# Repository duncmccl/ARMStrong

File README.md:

# ARMStrong
Microcontroller Learner board replacement for the BASYS MX3

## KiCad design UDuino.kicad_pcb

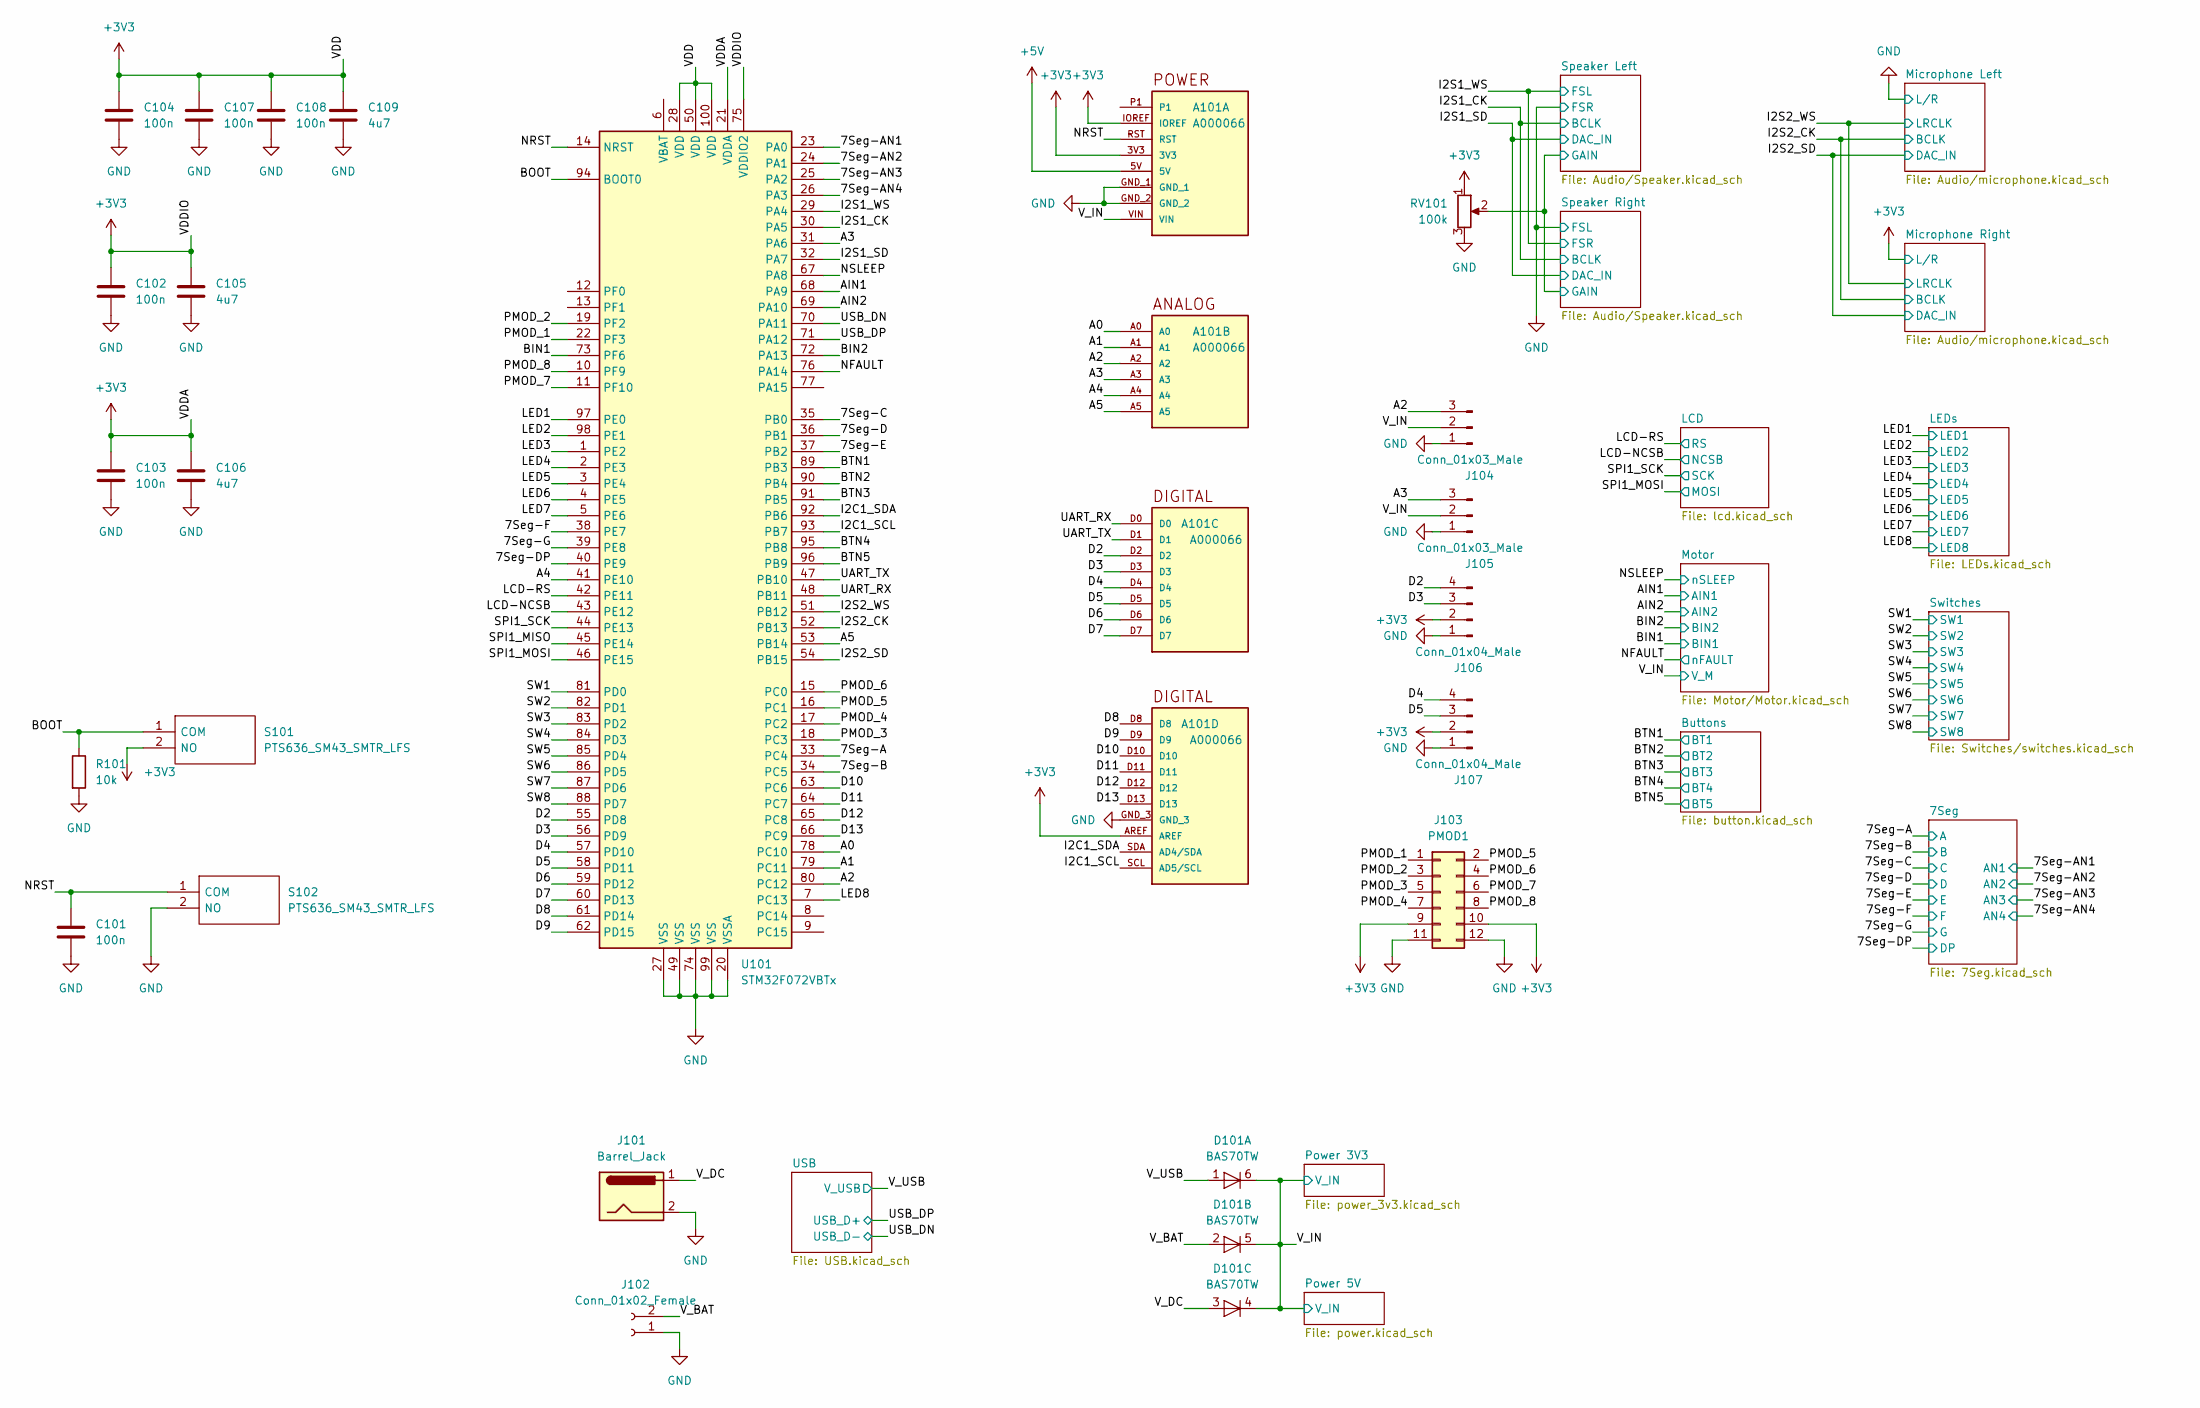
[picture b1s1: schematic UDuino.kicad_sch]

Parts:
A101: A000066; ARDUINO_A000066; Manufacturer_Part_Number A000066
C101, C102, C103, C104, C107, C108: 100n; C_0805_2012Metric; Manufacturer_Part_Number CL21B104KCFNNNE
C105, C106, C109: 4u7; C_0603_1608Metric; Manufacturer_Part_Number CL10A475KO8NNNC
D101: BAS70TW; SOT-363_SC-70-6; Manufacturer_Part_Number BAS70TW
J101: Barrel_Jack; BarrelJack_Horizontal; Manufacturer_Part_Number G-1005B
J102: Conn_01x02_Female; JST_XH_B2B-XH-AM_1x02_P2.50mm_Vertical
J103: PMOD1; PinSocket_2x06_P2.54mm_Horizontal
J104, J105: Conn_01x03_Male; PinHeader_1x03_P2.54mm_Vertical
J106, J107: Conn_01x04_Male; PinHeader_1x04_P2.54mm_Vertical
R101: 10k; R_0603_1608Metric; Manufacturer_Part_Number 0603WAF1002T5E
RV101: 100k; TRIM_3352T-1-104LF
S101, S102: PTS636_SM43_SMTR_LFS; PTS636SM43SMTRLFS; Mouser Part Number 611-PTS636SM43SMTRLF
U101: STM32F072VBTx; LQFP-100_14x14mm_P0.5mm

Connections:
+3V3: A101.3V3, A101.AREF, A101.IOREF, C102.2, C103.2, C104.2, C105.2, C106.2, C107.2, C108.2, C109.2, J103.9, J103.10, J106.2, J107.2, RV101.1, S101.2 (NO), U101.21 (VDDA), U101.28 (VDD), U101.50 (VDD), U101.75 (VDDIO2), U101.100 (VDD); also elsewhere on the board
+5V: A101.5V; also elsewhere on the board
/7Seg-A: U101.33 (PC4); also elsewhere on the board
/7Seg-AN1: U101.23 (PA0); also elsewhere on the board
/7Seg-AN2: U101.24 (PA1); also elsewhere on the board
/7Seg-AN3: U101.25 (PA2); also elsewhere on the board
/7Seg-AN4: U101.26 (PA3); also elsewhere on the board
/7Seg-B: U101.34 (PC5); also elsewhere on the board
/7Seg-C: U101.35 (PB0); also elsewhere on the board
/7Seg-D: U101.36 (PB1); also elsewhere on the board
/7Seg-DP: U101.40 (PE9); also elsewhere on the board
/7Seg-E: U101.37 (PB2); also elsewhere on the board
/7Seg-F: U101.38 (PE7); also elsewhere on the board
/7Seg-G: U101.39 (PE8); also elsewhere on the board
/A0: A101.A0, U101.78 (PC10)
/A1: A101.A1, U101.79 (PC11)
/A2: A101.A2, J104.3, U101.80 (PC12)
/A3: A101.A3, J105.3, U101.31 (PA6)
/A4: A101.A4, U101.41 (PE10)
/A5: A101.A5, U101.53 (PB14)
/AIN1: U101.68 (PA9); also elsewhere on the board
/AIN2: U101.69 (PA10); also elsewhere on the board
/BIN1: U101.73 (PF6); also elsewhere on the board
/BIN2: U101.72 (PA13); also elsewhere on the board
/BOOT: R101.1, S101.1 (COM), U101.94 (BOOT0)
/BTN1: U101.89 (PB3); also elsewhere on the board
/BTN2: U101.90 (PB4); also elsewhere on the board
/BTN3: U101.91 (PB5); also elsewhere on the board
/BTN4: U101.95 (PB8); also elsewhere on the board
/BTN5: U101.96 (PB9); also elsewhere on the board
/D2: A101.D2, J106.4, U101.55 (PD8)
/D3: A101.D3, J106.3, U101.56 (PD9)
/D4: A101.D4, J107.4, U101.57 (PD10)
/D5: A101.D5, J107.3, U101.58 (PD11)
/D6: A101.D6, U101.59 (PD12)
/D7: A101.D7, U101.60 (PD13)
/D8: A101.D8, U101.61 (PD14)
/D9: A101.D9, U101.62 (PD15)
/D10: A101.D10, U101.63 (PC6)
/D11: A101.D11, U101.64 (PC7)
/D12: A101.D12, U101.65 (PC8)
/D13: A101.D13, U101.66 (PC9)
/I2C1_SCL: A101.SCL (AD5/SCL), U101.93 (PB7)
/I2C1_SDA: A101.SDA (AD4/SDA), U101.92 (PB6)
/I2S1_CK: U101.30 (PA5); also elsewhere on the board
/I2S1_SD: U101.32 (PA7); also elsewhere on the board
/I2S1_WS: U101.29 (PA4); also elsewhere on the board
/I2S2_CK: U101.52 (PB13); also elsewhere on the board
/I2S2_SD: U101.54 (PB15); also elsewhere on the board
/I2S2_WS: U101.51 (PB12); also elsewhere on the board
/LCD-NCSB: U101.43 (PE12); also elsewhere on the board
/LCD-RS: U101.42 (PE11); also elsewhere on the board
/LED1: U101.97 (PE0); also elsewhere on the board
/LED2: U101.98 (PE1); also elsewhere on the board
/LED3: U101.1 (PE2); also elsewhere on the board
/LED4: U101.2 (PE3); also elsewhere on the board
/LED5: U101.3 (PE4); also elsewhere on the board
/LED6: U101.4 (PE5); also elsewhere on the board
/LED7: U101.5 (PE6); also elsewhere on the board
/LED8: U101.7 (PC13); also elsewhere on the board
/NFAULT: U101.76 (PA14); also elsewhere on the board
/NRST: A101.RST, C101.2, S102.1 (COM), U101.14 (NRST)
/NSLEEP: U101.67 (PA8); also elsewhere on the board
/PMOD_1: J103.1, U101.22 (PF3)
/PMOD_2: J103.3, U101.19 (PF2)
/PMOD_3: J103.5, U101.18 (PC3)
/PMOD_4: J103.7, U101.17 (PC2)
/PMOD_5: J103.2, U101.16 (PC1)
/PMOD_6: J103.4, U101.15 (PC0)
/PMOD_7: J103.6, U101.11 (PF10)
/PMOD_8: J103.8, U101.10 (PF9)
/SPI1_MISO: U101.45 (PE14)
/SPI1_MOSI: U101.46 (PE15); also elsewhere on the board
/SPI1_SCK: U101.44 (PE13); also elsewhere on the board
/SW1: U101.81 (PD0); also elsewhere on the board
/SW2: U101.82 (PD1); also elsewhere on the board
/SW3: U101.83 (PD2); also elsewhere on the board
/SW4: U101.84 (PD3); also elsewhere on the board
/SW5: U101.85 (PD4); also elsewhere on the board
/SW6: U101.86 (PD5); also elsewhere on the board
/SW7: U101.87 (PD6); also elsewhere on the board
/SW8: U101.88 (PD7); also elsewhere on the board
/Speaker Left/GAIN: RV101.2; also elsewhere on the board
/UART_RX: A101.D0, U101.48 (PB11)
/UART_TX: A101.D1, U101.47 (PB10)
/USB_DN: U101.70 (PA11); also elsewhere on the board
/USB_DP: U101.71 (PA12); also elsewhere on the board
/V_BAT: D101.2 (A), J102.2
/V_DC: D101.3 (A), J101.1
/V_IN: A101.VIN, D101.4 (K), D101.5 (K), D101.6 (K), J104.2, J105.2; also elsewhere on the board
/V_USB: D101.1 (A); also elsewhere on the board
GND: A101.GND_1, A101.GND_2, A101.GND_3, C101.1, C102.1, C103.1, C104.1, C105.1, C106.1, C107.1, C108.1, C109.1, J101.2, J102.1, J103.11, J103.12, J104.1, J105.1, J106.1, J107.1, R101.2, RV101.3, S102.2 (NO), U101.20 (VSSA), U101.27 (VSS), U101.49 (VSS), U101.74 (VSS), U101.99 (VSS); also elsewhere on the board

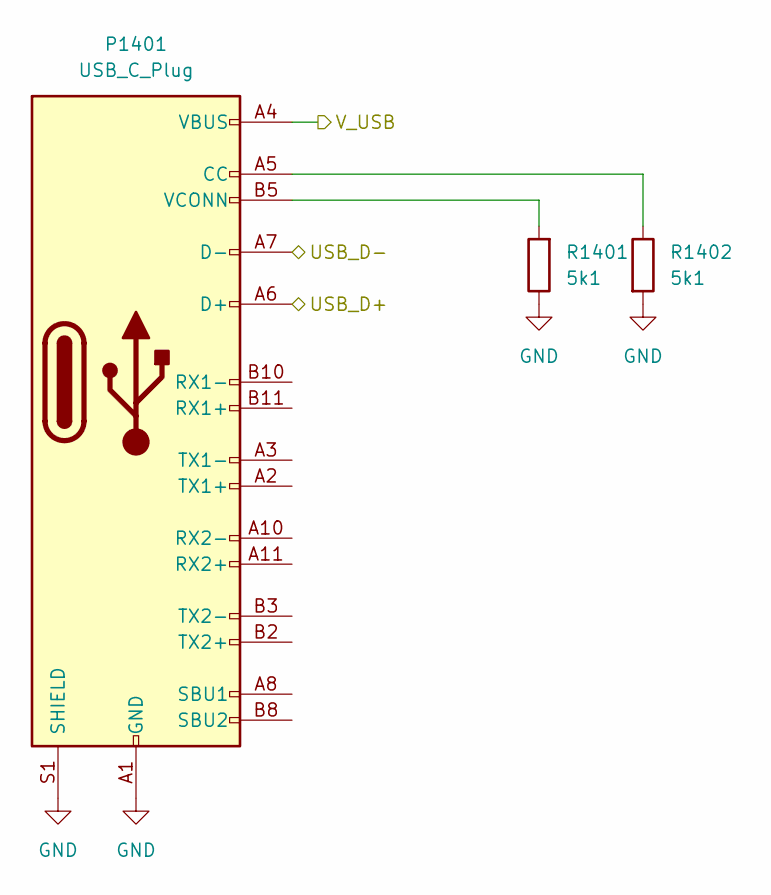
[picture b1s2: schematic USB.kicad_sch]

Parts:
P1401: USB_C_Plug; USB_C_Receptacle_Palconn_UTC16-G
R1401, R1402: 5k1; R_0603_1608Metric; Manufacturer_Part_Number 0603WAF5101T5E

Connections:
/USB_DN: P1401.A7 (D-); also elsewhere on the board
/USB_DP: P1401.A6 (D+); also elsewhere on the board
/V_USB: P1401.A4 (VBUS), P1401.A9 (VBUS), P1401.B4 (VBUS), P1401.B9 (VBUS); also elsewhere on the board
GND: P1401.A1 (GND), P1401.A12 (GND), P1401.B1 (GND), P1401.B12 (GND), P1401.S1 (SHIELD), R1401.1, R1402.2; also elsewhere on the board
unnamed: P1401.A5 (CC), R1402.1
unnamed: P1401.B5 (VCONN), R1401.2

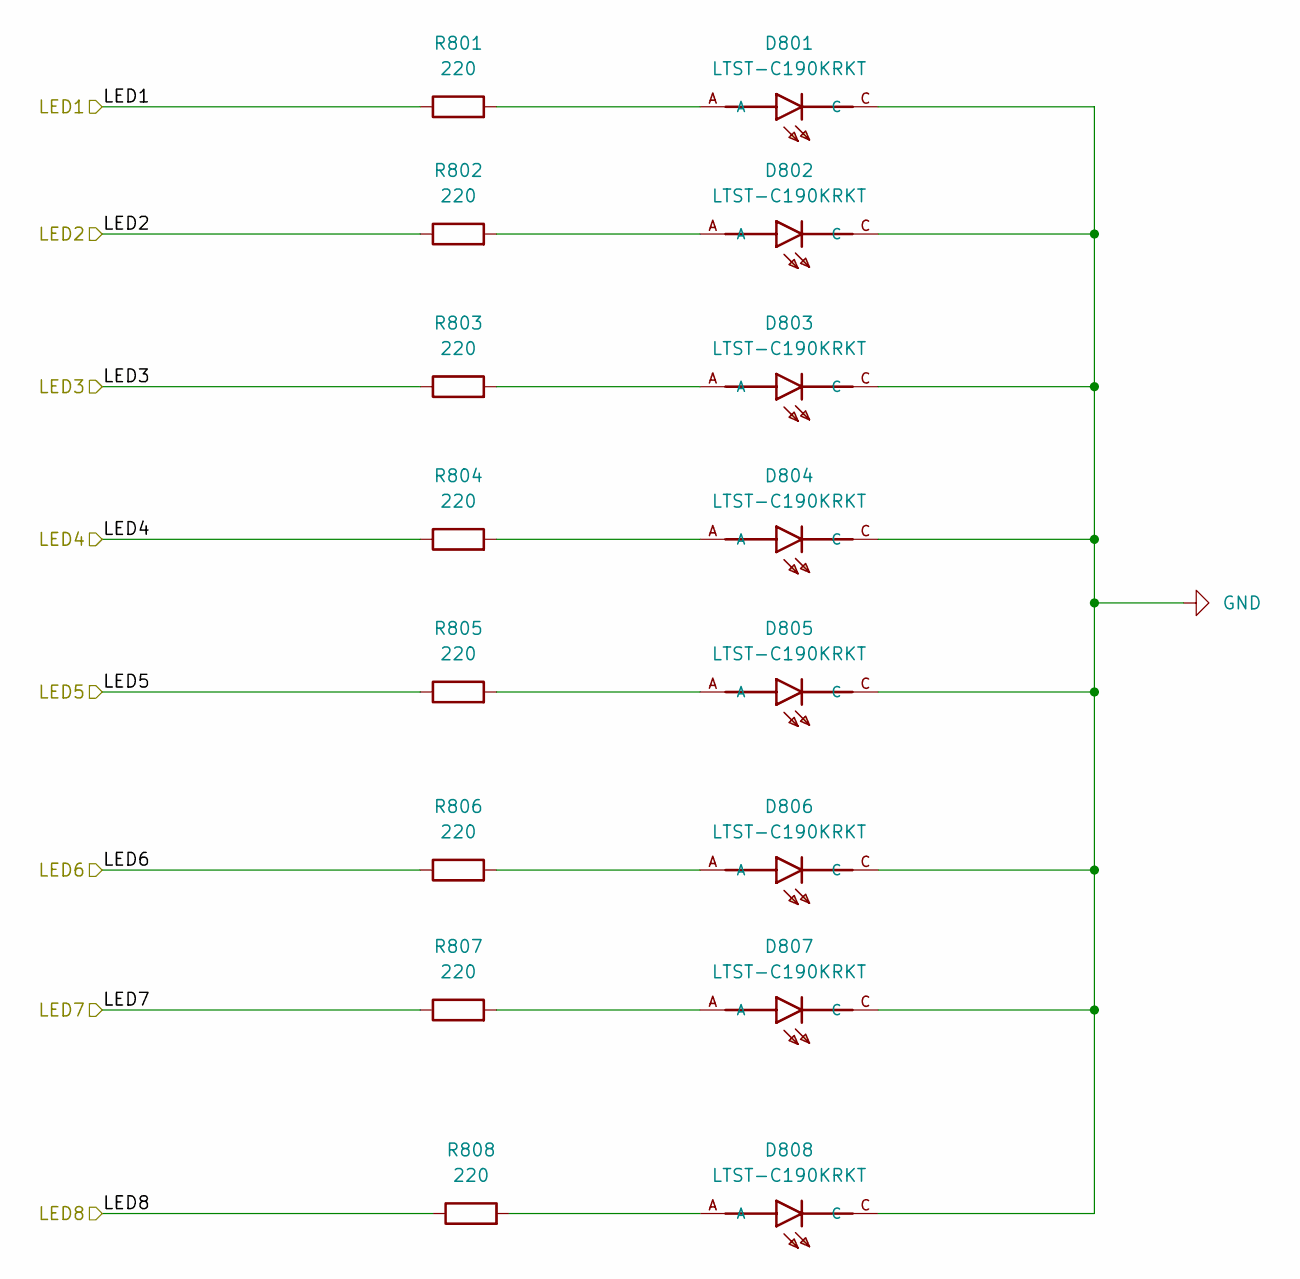
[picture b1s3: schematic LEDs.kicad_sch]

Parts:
D801, D802, D803, D804, D805, D806, D807, D808: LTST-C190KRKT; LEDC1608X35N; Manufacturer_Part_Number LTST-C190KRKT
R801, R802, R803, R804, R805, R806, R807, R808: 220; R_0603_1608Metric; Manufacturer_Part_Number 0603WAF2200T5E

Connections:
/LED1: R801.1; also elsewhere on the board
/LED2: R802.1; also elsewhere on the board
/LED3: R803.1; also elsewhere on the board
/LED4: R804.1; also elsewhere on the board
/LED5: R805.1; also elsewhere on the board
/LED6: R806.1; also elsewhere on the board
/LED7: R807.1; also elsewhere on the board
/LED8: R808.1; also elsewhere on the board
GND: D801.C, D802.C, D803.C, D804.C, D805.C, D806.C, D807.C, D808.C; also elsewhere on the board
unnamed: D801.A, R801.2
unnamed: D802.A, R802.2
unnamed: D803.A, R803.2
unnamed: D804.A, R804.2
unnamed: D805.A, R805.2
unnamed: D806.A, R806.2
unnamed: D807.A, R807.2
unnamed: D808.A, R808.2

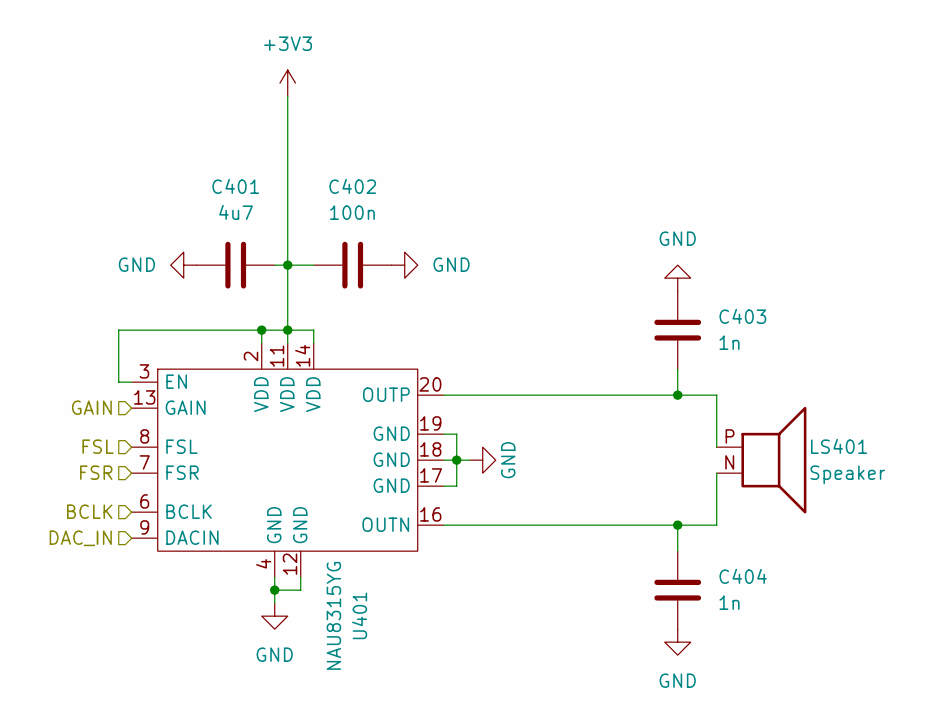
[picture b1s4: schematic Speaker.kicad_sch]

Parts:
C401: 4u7; C_0603_1608Metric; Manufacturer_Part_Number CL10A475KO8NNNC
C402: 100n; C_0805_2012Metric; Manufacturer_Part_Number CL21B104KCFNNNE
C403, C404: 1n; C_0603_1608Metric; Manufacturer_Part_Number CL10B102KB8NNNC
LS401: Speaker; SPKR_AS01508MS-SC11-WP-R
U401: NAU8315YG; QFN50P400X400X80-21N

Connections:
+3V3: C401.2, C402.1, U401.2 (VDD), U401.3 (EN), U401.11 (VDD), U401.14 (VDD); also elsewhere on the board
/I2S1_CK: U401.6 (BCLK); also elsewhere on the board
/I2S1_SD: U401.9 (DACIN); also elsewhere on the board
/I2S1_WS: U401.8 (FSL); also elsewhere on the board
/Speaker Left/GAIN: U401.13 (GAIN); also elsewhere on the board
GND: C401.1, C402.2, C403.1, C404.2, U401.4 (GND), U401.7 (FSR), U401.12 (GND), U401.17 (GND), U401.18 (GND), U401.19 (GND); also elsewhere on the board
unnamed: C403.2, LS401.P (1), U401.20 (OUTP)
unnamed: C404.1, LS401.N (2), U401.16 (OUTN)

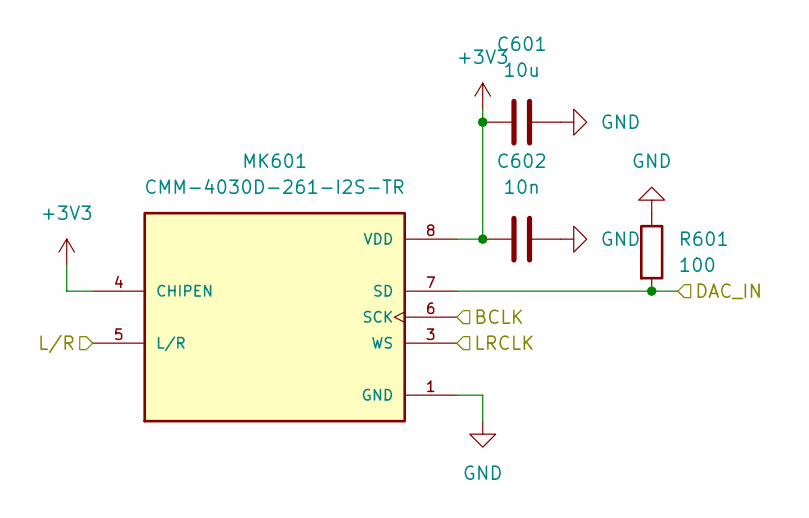
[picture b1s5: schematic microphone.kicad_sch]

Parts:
C601: 10u; C_0603_1608Metric; Manufacturer_Part_Number CL10A106KP8NNNC
C602: 10n; C_0603_1608Metric; Manufacturer_Part_Number 0603B103K500NT
MK601: CMM-4030D-261-I2S-TR; MIC_CMM-4030D-261-I2S-TR; PARTREV 1.0
R601: 100; R_0603_1608Metric; Manufacturer_Part_Number 0603WAF1000T5E

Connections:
+3V3: C601.1, C602.2, MK601.4 (CHIPEN), MK601.8 (VDD); also elsewhere on the board
/I2S2_CK: MK601.6 (SCK); also elsewhere on the board
/I2S2_SD: MK601.7 (SD), R601.2; also elsewhere on the board
/I2S2_WS: MK601.3 (WS); also elsewhere on the board
GND: C601.2, C602.1, MK601.1 (GND), MK601.5 (L/R), R601.1; also elsewhere on the board

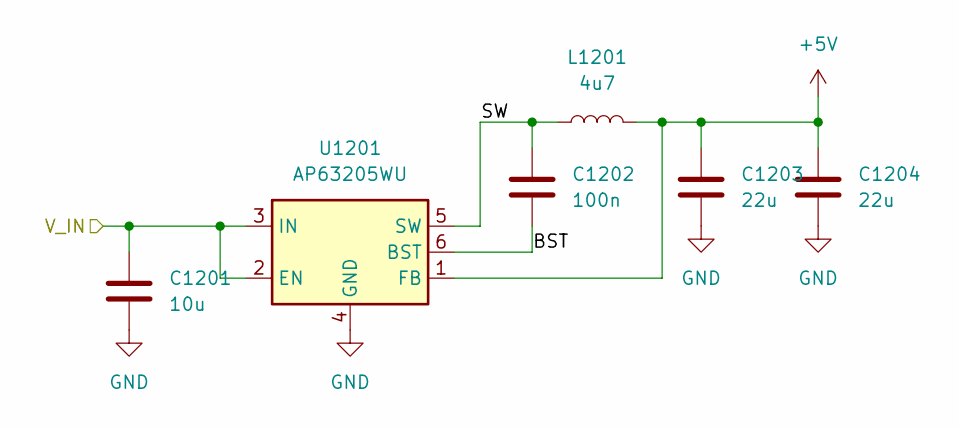
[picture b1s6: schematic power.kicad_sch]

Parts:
C1201: 10u; C_0603_1608Metric; Manufacturer_Part_Number CL10A106KP8NNNC
C1202: 100n; C_0805_2012Metric; Manufacturer_Part_Number CL21B104KCFNNNE
C1203, C1204: 22u; C_0603_1608Metric; Manufacturer_Part_Number CL10A226MQ8NRNC
L1201: 4u7; L_1008_2520Metric; Manufacturer_Part_Number CIGW252010GL4R7MNE
U1201: AP63205WU; TSOT-23-6

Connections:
+5V: C1203.1, C1204.1, L1201.2, U1201.1 (FB); also elsewhere on the board
/Power 5V/BST: C1202.2, U1201.6 (BST)
/Power 5V/SW: C1202.1, L1201.1, U1201.5 (SW)
/V_IN: C1201.1, U1201.2 (EN), U1201.3 (IN); also elsewhere on the board
GND: C1201.2, C1203.2, C1204.2, U1201.4 (GND); also elsewhere on the board

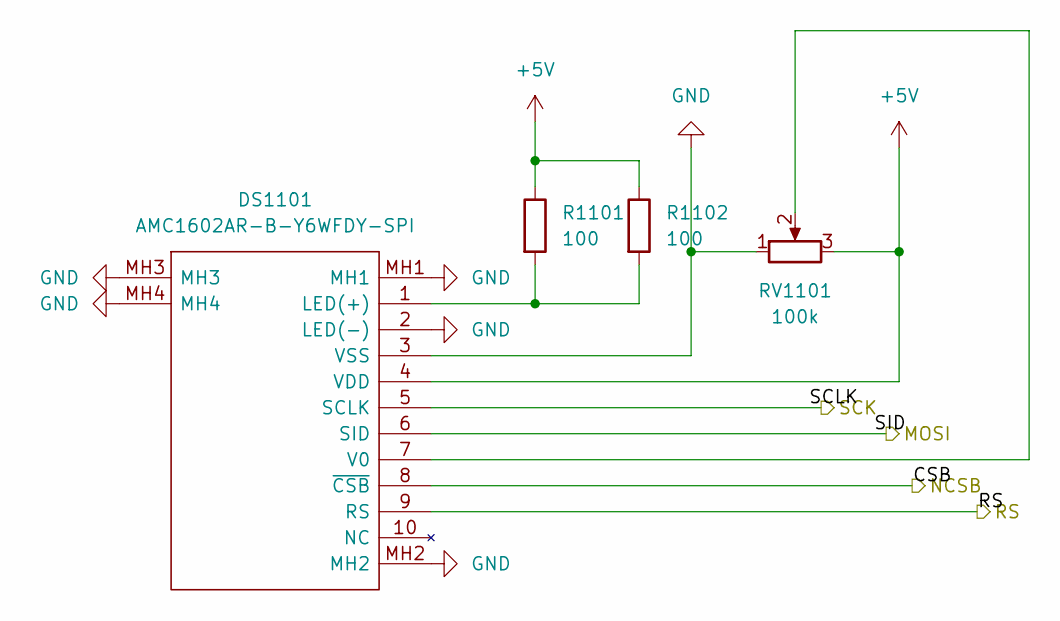
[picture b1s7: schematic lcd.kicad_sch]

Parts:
DS1101: AMC1602AR-B-Y6WFDY-SPI; AMC1602ARBY6WFDYSPI; Manufacturer_Part_Number AMC1602AR-B-Y6WFDY-SPI
R1101, R1102: 100; R_0603_1608Metric; Manufacturer_Part_Number 0603WAF1000T5E
RV1101: 100k; TRIM_3352T-1-104LF

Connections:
+5V: DS1101.4 (VDD), R1101.1, R1102.1, RV1101.3; also elsewhere on the board
/LCD-NCSB: DS1101.8 (~CSB); also elsewhere on the board
/LCD-RS: DS1101.9 (RS); also elsewhere on the board
/SPI1_MOSI: DS1101.6 (SID); also elsewhere on the board
/SPI1_SCK: DS1101.5 (SCLK); also elsewhere on the board
GND: DS1101.2 (LED(-)), DS1101.3 (VSS), DS1101.MH1, DS1101.MH2, DS1101.MH3, DS1101.MH4, RV1101.1; also elsewhere on the board
unnamed: DS1101.1 (LED(+)), R1101.2, R1102.2
unnamed: DS1101.7 (V0), RV1101.2

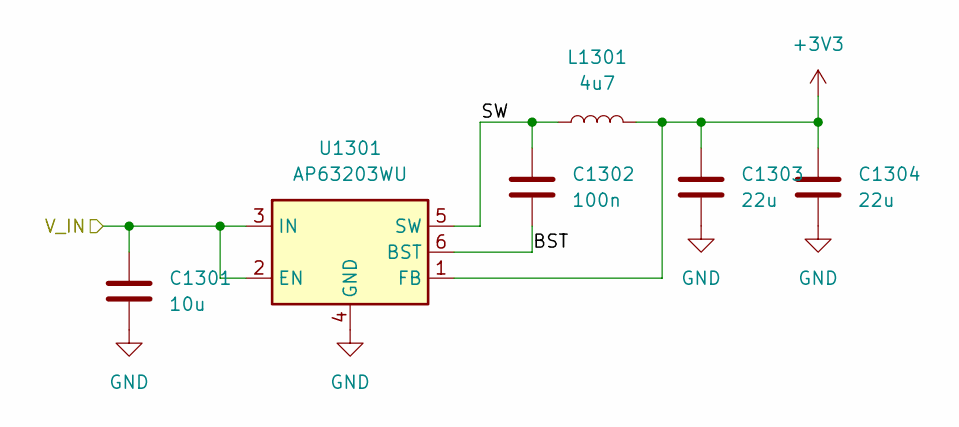
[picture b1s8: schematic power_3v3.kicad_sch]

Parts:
C1301: 10u; C_0603_1608Metric; Manufacturer_Part_Number CL10A106KP8NNNC
C1302: 100n; C_0805_2012Metric; Manufacturer_Part_Number CL21B104KCFNNNE
C1303, C1304: 22u; C_0603_1608Metric; Manufacturer_Part_Number CL10A226MQ8NRNC
L1301: 4u7; L_1008_2520Metric; Manufacturer_Part_Number CIGW252010GL4R7MNE
U1301: AP63203WU; TSOT-23-6

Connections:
+3V3: C1303.1, C1304.1, L1301.2, U1301.1 (FB); also elsewhere on the board
/Power 3V3/BST: C1302.2, U1301.6 (BST)
/Power 3V3/SW: C1302.1, L1301.1, U1301.5 (SW)
/V_IN: C1301.1, U1301.2 (EN), U1301.3 (IN); also elsewhere on the board
GND: C1301.2, C1303.2, C1304.2, U1301.4 (GND); also elsewhere on the board

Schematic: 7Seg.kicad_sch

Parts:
LED901: LDQ-M516RI; DIPS1524W50P254L5030H800Q12N
Q901, Q902, Q903, Q904: TRANS_PNP-MMBT4403; SOT-23
R901, R902, R903, R904: 1k; R_0603_1608Metric; Manufacturer_Part_Number 0603WAF1001T5E
R905, R906, R907, R908, R909, R910, R911, R912: 220; R_0603_1608Metric; Manufacturer_Part_Number 0603WAF2200T5E

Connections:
+5V: Q901.2 (E), Q902.2 (E), Q903.2 (E), Q904.2 (E); also elsewhere on the board
/7Seg-A: R905.2; also elsewhere on the board
/7Seg-AN1: R901.1; also elsewhere on the board
/7Seg-AN2: R902.1; also elsewhere on the board
/7Seg-AN3: R903.1; also elsewhere on the board
/7Seg-AN4: R904.1; also elsewhere on the board
/7Seg-B: R907.2; also elsewhere on the board
/7Seg-C: R909.2; also elsewhere on the board
/7Seg-D: R911.2; also elsewhere on the board
/7Seg-DP: R910.2; also elsewhere on the board
/7Seg-E: R912.2; also elsewhere on the board
/7Seg-F: R906.2; also elsewhere on the board
/7Seg-G: R908.2; also elsewhere on the board
unnamed: LED901.1, R912.1
unnamed: LED901.2, R911.1
unnamed: LED901.3, R910.1
unnamed: LED901.4, R909.1
unnamed: LED901.5, R908.1
unnamed: LED901.6, Q904.3 (C)
unnamed: LED901.7, R907.1
unnamed: LED901.8, Q901.3 (C)
unnamed: LED901.9, Q902.3 (C)
unnamed: LED901.10, R906.1
unnamed: LED901.11, R905.1
unnamed: LED901.12, Q903.3 (C)
unnamed: Q901.1 (B), R902.2
unnamed: Q902.1 (B), R903.2
unnamed: Q903.1 (B), R904.2
unnamed: Q904.1 (B), R901.2

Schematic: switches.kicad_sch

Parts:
R701, R702, R703, R704, R705, R706, R707, R708: 10k; R_0603_1608Metric; Manufacturer_Part_Number 0603WAF1002T5E
S701, S702, S703, S704, S705, S706, S707, S708: EG1218

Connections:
+3V3: S701.O, S702.O, S703.O, S704.O, S705.O, S706.O, S707.O, S708.O; also elsewhere on the board
/SW1: R708.1; also elsewhere on the board
/SW2: R707.1; also elsewhere on the board
/SW3: R706.1; also elsewhere on the board
/SW4: R705.1; also elsewhere on the board
/SW5: R704.1; also elsewhere on the board
/SW6: R703.1; also elsewhere on the board
/SW7: R702.1; also elsewhere on the board
/SW8: R701.1; also elsewhere on the board
GND: S701.S, S702.S, S703.S, S704.S, S705.S, S706.S, S707.S, S708.S; also elsewhere on the board
unnamed: R701.2, S701.P
unnamed: R702.2, S702.P
unnamed: R703.2, S703.P
unnamed: R704.2, S704.P
unnamed: R705.2, S705.P
unnamed: R706.2, S706.P
unnamed: R707.2, S707.P
unnamed: R708.2, S708.P

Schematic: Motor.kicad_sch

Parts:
C301: 10n; C_0603_1608Metric; Manufacturer_Part_Number 0603B103K500NT
C302: 10u; C_0603_1608Metric; Manufacturer_Part_Number CL10A106KP8NNNC
C303: 2u2; C_0603_1608Metric; Manufacturer_Part_Number CL10A225KO8NNNC
J301: Screw_Terminal_01x04; TerminalBlock_bornier-4_P5.08mm
U301: DRV8833RTY; Texas_S-PWQFN-N16_EP2.1x2.1mm

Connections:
/AIN1: U301.14 (AIN1); also elsewhere on the board
/AIN2: U301.13 (AIN2); also elsewhere on the board
/BIN1: U301.7 (BIN1); also elsewhere on the board
/BIN2: U301.8 (BIN2); also elsewhere on the board
/Motor/AOUT1: J301.1, U301.16 (AOUT1)
/Motor/AOUT2: J301.2, U301.2 (AOUT2)
/Motor/BOUT1: J301.4, U301.5 (BOUT1)
/Motor/BOUT2: J301.3, U301.3 (BOUT2)
/NFAULT: U301.6 (nFAULT); also elsewhere on the board
/NSLEEP: U301.15 (nSLEEP); also elsewhere on the board
/V_IN: C302.2, U301.10 (VM); also elsewhere on the board
GND: C301.1, C302.1, C303.1, U301.1 (AISEN), U301.4 (BISEN), U301.11 (GND), U301.17 (GND(PPAD)); also elsewhere on the board
unnamed: C301.2, U301.9 (VCP)
unnamed: C303.2, U301.12 (VINT)

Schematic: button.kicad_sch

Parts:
R1001, R1002, R1003, R1004, R1005: 10k; R_0603_1608Metric; Manufacturer_Part_Number 0603WAF1002T5E
S1001, S1002, S1003, S1004, S1005: PTS636_SM43_SMTR_LFS; PTS636SM43SMTRLFS; Mouser Part Number 611-PTS636SM43SMTRLF

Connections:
+3V3: S1001.1 (COM), S1002.1 (COM), S1003.1 (COM), S1004.1 (COM), S1005.1 (COM); also elsewhere on the board
/BTN1: R1001.2, S1001.2 (NO); also elsewhere on the board
/BTN2: R1002.2, S1002.2 (NO); also elsewhere on the board
/BTN3: R1003.2, S1003.2 (NO); also elsewhere on the board
/BTN4: R1004.2, S1004.2 (NO); also elsewhere on the board
/BTN5: R1005.2, S1005.2 (NO); also elsewhere on the board
GND: R1001.1, R1002.1, R1003.1, R1004.1, R1005.1; also elsewhere on the board
